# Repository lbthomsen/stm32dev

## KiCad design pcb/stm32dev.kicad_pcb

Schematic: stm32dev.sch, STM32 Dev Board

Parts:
C1, C3: 10uF; C_0805_2012Metric; LCSC C15850
C2, C5, C6, C7, C8, C14: 100nF; C_0402_1005Metric; LCSC C1525
C4: 1uF; C_0402_1005Metric; LCSC C52923
C9: 10nF; C_0402_1005Metric; LCSC C15195
C10, C11: 20pF; C_0402_1005Metric; LCSC C1554
C12, C13: 2.2uF; C_0603_1608Metric; LCSC C23630
D1, D5, D6, D7: WS2812C; LED_WS2812C-2020; LCSC C965556
D2: D_SOD-123; LCSC C8598
D3: GR; LED_0603_1608Metric; LCSC C72043
D4: BLUE; LED_0603_1608Metric; LCSC C72041
H1, H2, H3, H4: MountingHole_2.2mm_M2
J1: USB_C_Receptacle_HRO_TYPE-C-31-M-12; LCSC C165948
J2: PinHeader_2x03_P2.54mm_Horizontal
J3: Micro_SD_Card_Det; microSD_HC_Hirose_DM3D-SF
J4, J5: PinHeader_2x20_P2.54mm_Vertical
R1, R5: 10k; R_0402_1005Metric; LCSC C25744
R2, R3: 22R; R_0402_1005Metric; LCSC C25092
R6, R9: 220; R_0402_1005Metric; LCSC C25091
R7, R8: 5.1k; R_0402_1005Metric; LCSC C25905
SW1, SW2: TS-1088R-02526; LCSC C455281
U1: XC6206P332MR; SOT-23; LCSC C5446
U2: STM32F405RGTx; LQFP-64_10x10mm_P0.5mm; LCSC C15742
U3: W25Q128JVS; SOIC-8_5.23x5.23mm_P1.27mm
Y1: 16 MHz; Crystal_SMD_3225-4Pin_3.2x2.5mm; LCSC C13738

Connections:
+5V: C1.1, D2.1 (K), J5.37, J5.38, U1.3
BO0: R5.1, SW2.1, U2.60 (BOOT0)
GND: C1.2, C2.2, C3.2, C4.2, C5.2, C6.2, C7.2, C8.2, C9.2, C10.2, C11.2, C12.2, C13.2, C14.2, D1.2, D5.2, D6.2, D7.2, J1.A1, J1.A12, J1.B1, J1.B12, J1.S1, J2.5, J3.6 (VSS), J3.9 (DET_B), J3.11 (SHIELD), J4.1, J4.2, J4.39, J4.40, J5.39, J5.40, R5.2, R6.2, SW1.1, U1.1, U2.12 (VSSA), U2.18 (VSS), U2.63 (VSS), U3.4, Y1.2, Y1.4
NRST: C2.1, J2.1, R1.2, SW1.2, U2.7 (NRST)
unnamed: C10.1, U2.5 (PH0), Y1.1
unnamed: C11.1, U2.6 (PH1), Y1.3
unnamed: C12.1, U2.31 (VCAP_1)
unnamed: C13.1, U2.47 (VCAP_2)
unnamed: D1.1, D5.3
unnamed: D3.1, R6.1
unnamed: D4.1, R9.1
unnamed: D5.1, D6.3
unnamed: D6.1, D7.3
unnamed: J1.A5, R7.1
unnamed: J1.A6, J1.B6, R3.1
unnamed: J1.A7, J1.B7, R2.1
unnamed: J1.B5, R8.1
PA0: J4.11, J4.12, U2.14 (PA0)
PA1: J4.13, J4.14, U2.15 (PA1)
PA2: J4.15, J4.16, U2.16 (PA2)
PA3: J4.17, J4.18, U2.17 (PA3)
PA4: J4.19, J4.20, U2.20 (PA4)
PA5: J4.21, J4.22, U2.21 (PA5)
PA6: J4.23, J4.24, U2.22 (PA6)
PA7: J4.25, J4.26, U2.23 (PA7)
PA8: J5.23, J5.24, U2.41 (PA8)
PA9: J5.21, J5.22, U2.42 (PA9)
PA10: J5.19, J5.20, U2.43 (PA10)
PA11: J5.17, J5.18, R2.2, U2.44 (PA11)
PA12: J5.15, J5.16, R3.2, U2.45 (PA12)
PA15: J5.13, J5.14, U2.50 (PA15)
PB0: J4.31, J4.32, U2.26 (PB0)
PB1: J4.33, J4.34, U2.27 (PB1)
PB2: J4.35, J4.36, U2.28 (PB2)
PB3: U3.6
PB4: J5.11, J5.12, U2.56 (PB4), U3.2
PB5: J5.9, J5.10, U2.57 (PB5), U3.5
PB6: J5.7, J5.8, U2.58 (PB6), U3.1
PB7: J5.5, J5.6, U2.59 (PB7)
PB8: J5.3, J5.4, U2.61 (PB8)
PB9: J5.1, J5.2, U2.62 (PB9)
PB10: J5.35, J5.36, U2.29 (PB10)
PB11: J5.33, J5.34, U2.30 (PB11)
PB12: J5.31, J5.32, U2.33 (PB12)
PB13: J5.29, J5.30, U2.34 (PB13)
PB14: J5.27, J5.28, U2.35 (PB14)
PB15: J5.25, J5.26, U2.36 (PB15)
PC0: J4.3, J4.4, U2.8 (PC0)
PC1: J4.5, J4.6, U2.9 (PC1)
PC2: J4.7, J4.8, U2.10 (PC2)
PC3: J4.9, J4.10, U2.11 (PC3)
PC4: J4.27, J4.28, U2.24 (PC4)
PC5: J4.29, J4.30, U2.25 (PC5)
PC6: D1.3, U2.37 (PC6)
PC13: R9.2, U2.2 (PC13)
SD_CLK: J3.5 (CLK), U2.53 (PC12)
SD_CMD: J3.3 (CMD), U2.54 (PD2)
SD_D0: J3.7 (DAT0), U2.39 (PC8)
SD_D1: J3.8 (DAT1), U2.40 (PC9)
SD_D2: J3.1 (DAT2), U2.51 (PC10)
SD_D3: J3.2 (DAT3/CD), U2.52 (PC11)
SD_DET: J3.10 (DET_A), U2.38 (PC7)
SWCLK: J2.3, U2.49 (PA14)
SWDIO: J2.4, U2.46 (PA13)
SWO: J2.6, U2.55 (PB3)
UCC: R7.2, R8.2, U2.3 (PC14)
VBUS: D2.2 (A), J1.A4, J1.A9, J1.B4, J1.B9

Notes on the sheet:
USB C Connection

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
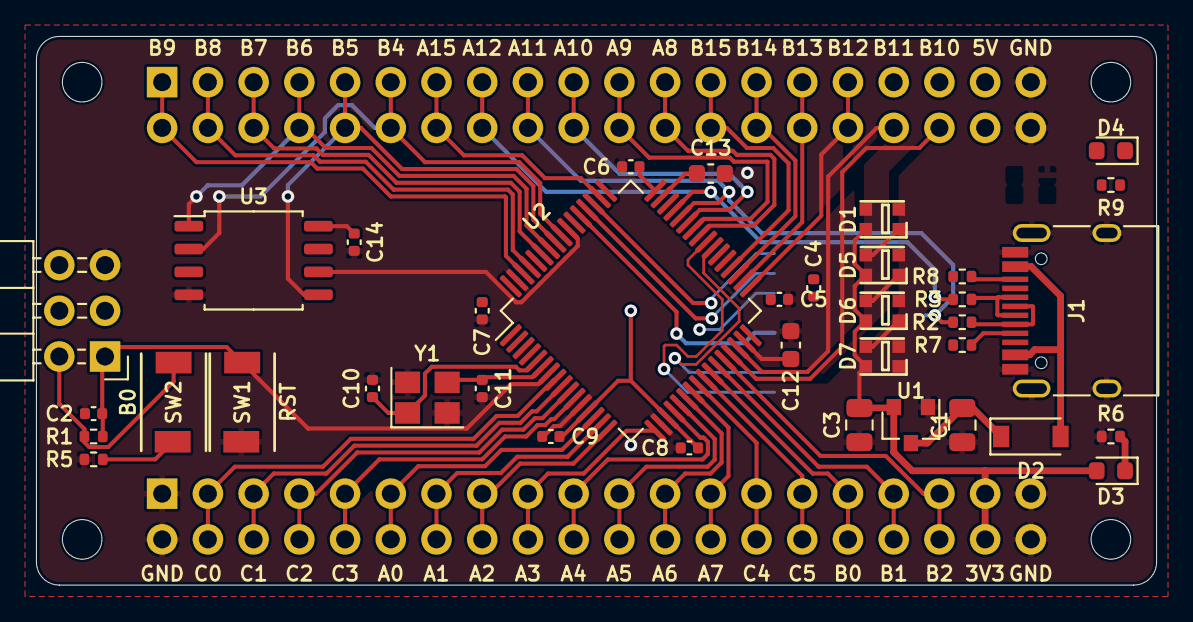
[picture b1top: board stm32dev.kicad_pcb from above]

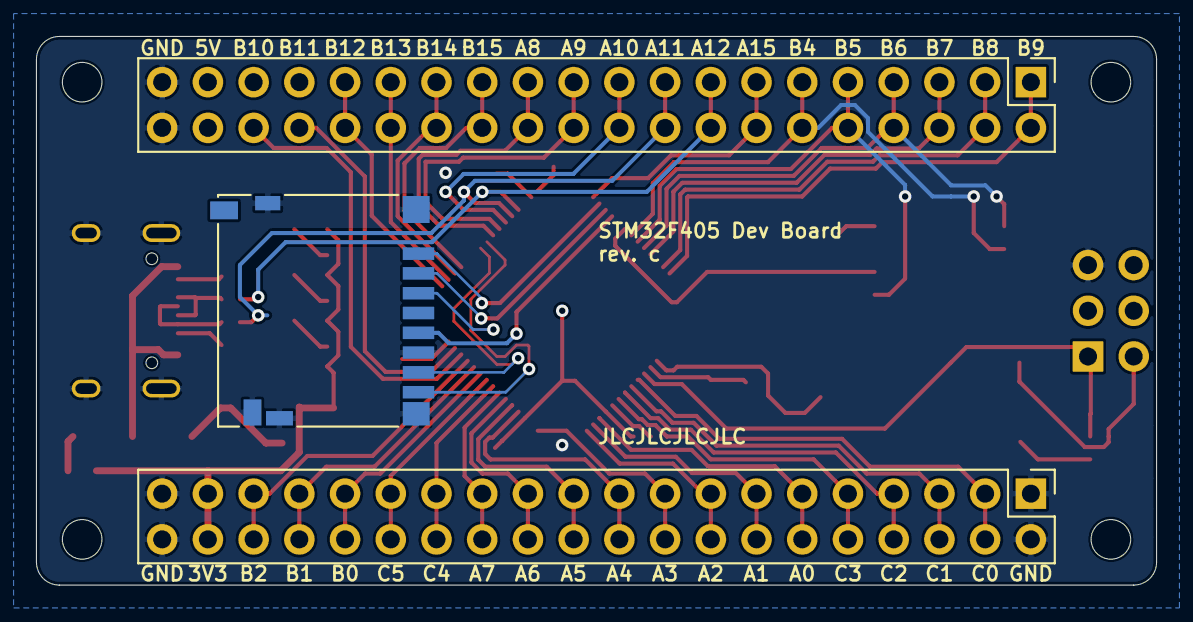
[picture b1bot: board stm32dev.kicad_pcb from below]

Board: 2 copper layers, 62.2 x 30.5 mm, 44 parts (3 on the bottom side), 67 nets.

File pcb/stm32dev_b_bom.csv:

Comment,Designator,Footprint,LCSC
"10uF","C1,C3","Capacitor_SMD:C_0805_2012Metric","C15850"
"20pF","C10,C11","Capacitor_SMD:C_0402_1005Metric","C1554"
"2.2uF","C13,C12","Capacitor_SMD:C_0402_1005Metric","C12530"
"1uF","C4","Capacitor_SMD:C_0402_1005Metric","C52923"
"100nF","C5,C6,C7,C8,C2","Capacitor_SMD:C_0402_1005Metric","C1525"
"10nF","C9","Capacitor_SMD:C_0402_1005Metric","C15195"
"WS2812B","D1","LED_SMD:LED_WS2812B_PLCC4_5.0x5.0mm_P3.2mm","C114586"
"~","D2","Diode_SMD:D_SOD-123","C8598"
"YEL","D3","LED_SMD:LED_0603_1608Metric","C72038"
"BLUE","D4","LED_SMD:LED_0603_1608Metric","C72041"
"USB_C_Receptacle_USB2.0","J1","Connector_USB:USB_C_Receptacle_HRO_TYPE-C-31-M-12","C167321"
"~","J2","Connector_PinHeader_2.54mm:PinHeader_2x03_P2.54mm_Horizontal"
"Micro_SD_Card_Det","J3","Connector_Card:microSD_HC_Hirose_DM3D-SF"
"~","J4,J5","Connector_PinHeader_2.54mm:PinHeader_2x20_P2.54mm_Vertical"
"NM","R1,R5","Resistor_SMD:R_0402_1005Metric"
"22R","R2,R3","Resistor_SMD:R_0402_1005Metric","C25092"
"1.5k","R4","Resistor_SMD:R_0402_1005Metric","C25867"
"5.1k","R7,R8","Resistor_SMD:R_0402_1005Metric","C25905"
"1k","R9,R6","Resistor_SMD:R_0402_1005Metric","C25905"
"~","SW1,SW2","Button_Switch_SMD:SW_SPST_TL3342","C318887"
"XC6206P332MR","U1","Package_TO_SOT_SMD:SOT-23","C5446"
"STM32F405RGTx","U2","Package_QFP:LQFP-64_10x10mm_P0.5mm","C15742"
"8 MHz","Y1","Crystal:Crystal_SMD_Abracon_ABM3-2Pin_5.0x3.2mm","C115962"

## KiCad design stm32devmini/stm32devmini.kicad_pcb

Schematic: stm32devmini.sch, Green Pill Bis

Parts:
C1, C2: 10uF; C_0805_2012Metric; LCSC C15850
C3, C6, C8, C9, C10: 100nF; C_0402_1005Metric; LCSC C1525
C5, C7, C11, C12: 20pF; C_0402_1005Metric; LCSC C1554
D1: D_SOD-123; LCSC C8598
D2: YEL; LED_0603_1608Metric; LCSC C72038
D3: BLUE; LED_0603_1608Metric; LCSC C72041
J1: USB_C_Receptacle_USB2.0; USB_C_Receptacle_HRO_TYPE-C-31-M-12; LCSC C167321
J2, J3: PinHeader_1x20_P2.54mm_Vertical
J4: PinHeader_1x04_P2.54mm_Horizontal
R1, R2: 22R; R_0402_1005Metric; LCSC C25092
R3: 1.5k; R_0402_1005Metric; LCSC C25867
R4, R5: 5.1k; R_0402_1005Metric; LCSC C25905
R6, R9: NM; R_0402_1005Metric
R7, R8: 1k; R_0402_1005Metric; LCSC C25905
SW1, SW2: SW_SPST_TL3342; LCSC C318887
U1: XC6206P332MR; SOT-23; LCSC C5446
U2: STM32F103C8T6; LQFP-48_7x7mm_P0.5mm; LCSC C8734
Y1: 8M; Crystal_SMD_Abracon_ABM3-2Pin_5.0x3.2mm; LCSC C115962
Y2: 32.768k; Crystal_SMD_EuroQuartz_EQ161-2Pin_3.2x1.5mm; LCSC C32346

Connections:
+3V3: C2.1, C6.1, C8.1, C9.1, C10.1, D2.2 (A), D3.2 (A), J2.18, J4.1, R3.2, R6.1, SW2.2, U1.2, U2.1 (VBAT), U2.9 (VDDA), U2.24 (VDD), U2.36 (VDD), U2.48 (VDD)
+5V: C1.1, D1.1 (K), J2.19, U1.3
A0: J2.5, U2.10 (PA0)
A1: J2.6, U2.11 (PA1)
A2: J2.7, U2.12 (PA2)
A3: J2.8, U2.13 (PA3)
A4: J2.9, U2.14 (PA4)
A5: J2.10, U2.15 (PA5)
A6: J2.11, U2.16 (PA6)
A7: J2.12, U2.17 (PA7)
A8: J3.16, U2.29 (PA8)
A9: J3.15, U2.30 (PA9)
A10: J3.14, U2.31 (PA10)
A11: J3.13, R1.2, U2.32 (PA11)
A12: J3.12, R2.2, U2.33 (PA12)
A15: J3.11, U2.38 (PA15)
B0: J2.13, U2.18 (PB0)
B1: J2.14, U2.19 (PB1)
B2: J2.15, U2.20 (PB2)
B3: J3.10, U2.39 (PB3)
B4: J3.9, U2.40 (PB4)
B5: J3.8, U2.41 (PB5)
B6: J3.7, U2.42 (PB6)
B7: J3.6, U2.43 (PB7)
B8: J3.5, U2.45 (PB8)
B9: J3.4, U2.46 (PB9)
B10: J2.16, U2.21 (PB10)
B11: J2.17, U2.22 (PB11)
B12: J3.20, U2.25 (PB12)
B13: J3.19, U2.26 (PB13)
B14: J3.18, U2.27 (PB14)
B15: J3.17, U2.28 (PB15)
BO0: J3.3, R9.1, SW2.1, U2.44 (BOOT0)
C13: J2.2, R7.2, U2.2 (PC13)
C14: C11.1, J2.3, U2.3 (PC14), Y2.1
C15: C12.1, J2.4, U2.4 (PC15), Y2.2
GND: C1.2, C2.2, C3.2, C5.2, C6.2, C7.2, C8.2, C9.2, C10.2, C11.2, C12.2, J1.A1, J1.A12, J1.B1, J1.B12, J1.S1, J2.1, J2.20, J3.1, J4.4, R4.2, R5.2, R8.2, R9.2, SW1.1, U1.1, U2.8 (VSSA), U2.23 (VSS), U2.35 (VSS), U2.47 (VSS)
unnamed: C5.1, U2.5 (PD0), Y1.1
unnamed: C7.1, U2.6 (PD1), Y1.2
unnamed: D2.1 (K), R8.1
unnamed: D3.1 (K), R7.1
unnamed: J1.A5, R5.1
unnamed: J1.A6, J1.B6, R2.1, R3.1
unnamed: J1.A7, J1.B7, R1.1
unnamed: J1.B5, R4.1
RST: C3.1, J3.2, R6.2, SW1.2, U2.7 (NRST)
SWCLK: J4.3, U2.37 (PA14)
SWDIO: J4.2, U2.34 (PA13)
VBUS: D1.2 (A), J1.A4, J1.A9, J1.B4, J1.B9

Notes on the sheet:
Internal pull-up
Power Regulation
Decoupling
USB C Connection
NOTICE! Headers are mostly but NOT 100 % compatible with the blue/black pill.

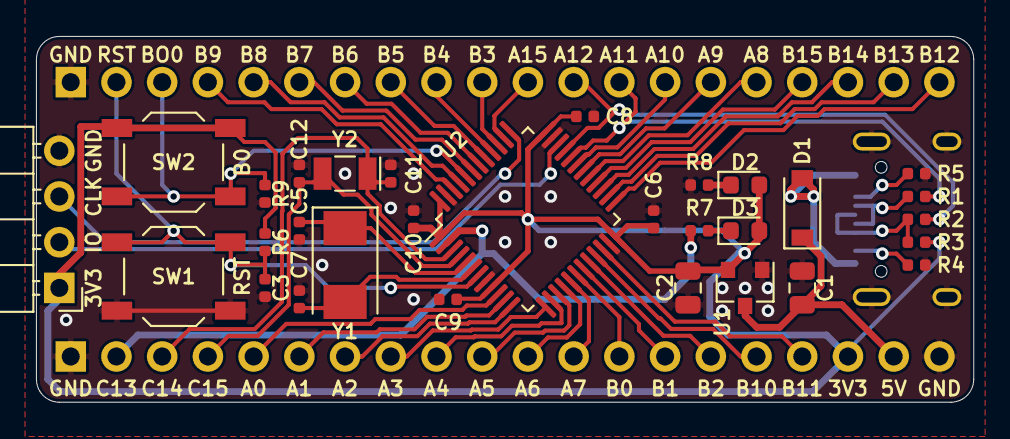
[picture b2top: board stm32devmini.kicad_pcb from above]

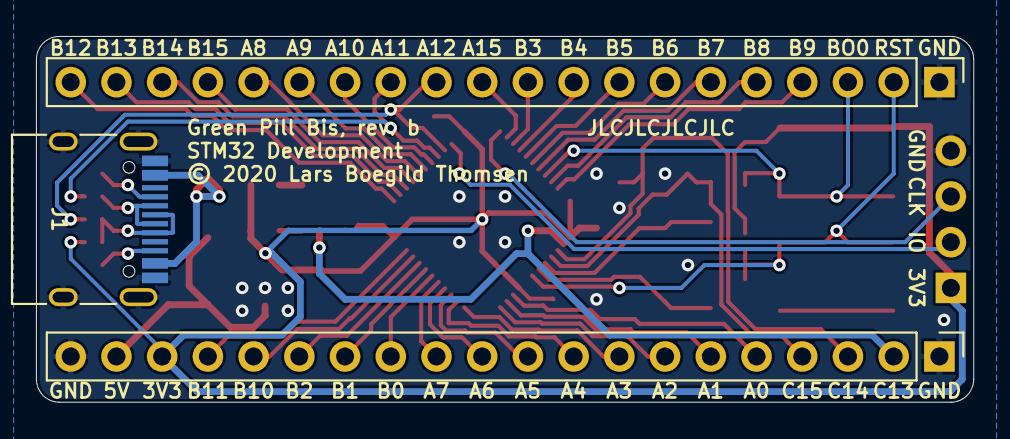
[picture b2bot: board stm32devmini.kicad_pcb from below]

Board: 2 copper layers, 52.1 x 20.3 mm, 33 parts (3 on the bottom side), 49 nets.

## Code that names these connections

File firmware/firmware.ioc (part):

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PC3.Mode=Full_Duplex_Master
PH0-OSC_IN.Signal=RCC_OSC_IN
Mcu.UserName=STM32F405RGTx
PB10.Mode=Full_Duplex_Master
PC12.Signal=SDIO_CK
PC10.Signal=SDIO_D2
PA12.GPIOParameters=GPIO_Speed
PB15.Signal=USB_OTG_HS_DP
PB13.Signal=CAN2_TX
RCC.SYSCLKSource=RCC_SYSCLKSOURCE_PLLCLK
PB5.GPIOParameters=GPIO_PuPd
PA12.Signal=GPIO_Output
PB6.Signal=I2C1_SCL
PC7.Signal=GPIO_Input
PB6.Mode=I2C
PC3.Signal=SPI2_MOSI
PH0-OSC_IN.Mode=HSE-External-Oscillator
RCC.HSE_VALUE=16000000
PB3.Mode=JTAG_5_pins
PA15.Mode=JTAG_5_pins
PB4.Mode=JTAG_5_pins
PA14.Mode=JTAG_5_pins
PB14.Mode=Device_Only_FS
PC9.Mode=SD_4_bits_Wide_bus
PB7.Signal=I2C1_SDA
PH1-OSC_OUT.Mode=HSE-External-Oscillator
Mcu.Package=LQFP64
PB9.Signal=CAN1_TX
PA6.Signal=ADCx_IN6
PB12.Mode=Slave
PA10.Signal=USART1_RX
PA15.Signal=SYS_JTDI
PC11.Mode=SD_4_bits_Wide_bus
PB13.Mode=Slave
PA12.GPIO_Speed=GPIO_SPEED_FREQ_LOW
PB4.Signal=SYS_JTRST
PA3.Signal=USART2_RX
PA10.Mode=Asynchronous
PC11.Signal=SDIO_D3
PC8.Signal=SDIO_D0
PC2.Signal=SPI2_MISO
PC6.Signal=GPIO_Input
PC10.Mode=SD_4_bits_Wide_bus
PC2.Mode=Full_Duplex_Master
PA13.Signal=SYS_JTMS-SWDIO
PA3.Mode=Asynchronous
PA9.Mode=Asynchronous
PB9.Mode=Master
PA9.Signal=USART1_TX
PB10.Signal=SPI2_SCK
PB14.Signal=USB_OTG_HS_DM
PD2.Mode=SD_4_bits_Wide_bus
PA5.Signal=COMP_DAC2_group
PC12.Mode=SD_4_bits_Wide_bus
board=custom
PB15.Mode=Device_Only_FS
PH1-OSC_OUT.Signal=RCC_OSC_OUT
PA13.Mode=JTAG_5_pins
Mcu.Name=STM32F405RGTx
PA2.Signal=USART2_TX
PC8.Mode=SD_4_bits_Wide_bus
PB3.Signal=SYS_JTDO-SWO
PA4.Signal=COMP_DAC1_group
RCC.SYSCLKFreq_VALUE=72000000
PB5.Signal=GPIO_Input
PB5.GPIO_PuPd=GPIO_PULLUP
PB7.Mode=I2C
PA14.Signal=SYS_JTCK-SWCLK
PB8.Mode=Master
PA2.Mode=Asynchronous
PB8.Signal=CAN1_RX
PC9.Signal=SDIO_D1
PD2.Signal=SDIO_CMD
PB12.Signal=CAN2_RX
PA7.Signal=ADCx_IN7

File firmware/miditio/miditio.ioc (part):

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Mcu.Name=STM32F405RGTx
Mcu.Package=LQFP64
Mcu.UserName=STM32F405RGTx
PA0-WKUP.Signal=ADCx_IN0
PA1.Signal=ADCx_IN1
PA10.Mode=Asynchronous
PA10.Signal=USART1_RX
PA11.Mode=Device_Only
PA11.Signal=USB_OTG_FS_DM
PA12.Mode=Device_Only
PA12.Signal=USB_OTG_FS_DP
PA13.Mode=Serial_Wire
PA13.Signal=SYS_JTMS-SWDIO
PA14.Mode=Serial_Wire
PA14.Signal=SYS_JTCK-SWCLK
PA4.Signal=COMP_DAC1_group
PA5.Signal=COMP_DAC2_group
PA9.Mode=Asynchronous
PA9.Signal=USART1_TX
PC13-ANTI_TAMP.GPIOParameters=PinState,GPIO_Label
PC13-ANTI_TAMP.GPIO_Label=LED
PC13-ANTI_TAMP.PinState=GPIO_PIN_SET
PC13-ANTI_TAMP.Signal=GPIO_Output
PH0-OSC_IN.Mode=HSE-External-Oscillator
PH0-OSC_IN.Signal=RCC_OSC_IN
PH1-OSC_OUT.Mode=HSE-External-Oscillator
PH1-OSC_OUT.Signal=RCC_OSC_OUT
RCC.HSE_VALUE=8000000
RCC.SYSCLKFreq_VALUE=168000000
RCC.SYSCLKSource=RCC_SYSCLKSOURCE_PLLCLK
board=custom

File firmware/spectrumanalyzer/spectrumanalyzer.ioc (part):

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Mcu.Name=STM32F405RGTx
Mcu.Package=LQFP64
Mcu.UserName=STM32F405RGTx
PA0-WKUP.Signal=ADCx_IN0
PA13.Mode=Serial_Wire
PA13.Signal=SYS_JTMS-SWDIO
PA14.Mode=Serial_Wire
PA14.Signal=SYS_JTCK-SWCLK
PA4.Signal=COMP_DAC1_group
PA5.Signal=COMP_DAC2_group
PA6.GPIOParameters=GPIO_Label
PA6.GPIO_Label=P0
PA6.Signal=ADCx_IN6
PA7.GPIOParameters=GPIO_Label
PA7.GPIO_Label=P1
PA7.Signal=ADCx_IN7
PC0.GPIOParameters=GPIO_Label
PC0.GPIO_Label=DBG0
PC0.Signal=GPIO_Output
PC1.GPIOParameters=GPIO_Label
PC1.GPIO_Label=DBG1
PC1.Signal=GPIO_Output
PC13-ANTI_TAMP.GPIOParameters=PinState,GPIO_Label
PC13-ANTI_TAMP.GPIO_Label=BUILTIN_LED
PC13-ANTI_TAMP.PinState=GPIO_PIN_SET
PC13-ANTI_TAMP.Signal=GPIO_Output
PH0-OSC_IN.Mode=HSE-External-Oscillator
PH0-OSC_IN.Signal=RCC_OSC_IN
PH1-OSC_OUT.Mode=HSE-External-Oscillator
PH1-OSC_OUT.Signal=RCC_OSC_OUT
RCC.HSE_VALUE=8000000
RCC.SYSCLKFreq_VALUE=168000000
RCC.SYSCLKSource=RCC_SYSCLKSOURCE_PLLCLK
board=custom

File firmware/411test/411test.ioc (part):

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Mcu.Name=STM32F411C(C-E)Ux
Mcu.Package=UFQFPN48
Mcu.UserName=STM32F411CEUx
PA13.Mode=Trace_Asynchronous_SW
PA13.Signal=SYS_JTMS-SWDIO
PA14.Mode=Trace_Asynchronous_SW
PA14.Signal=SYS_JTCK-SWCLK
PA6.Signal=S_TIM3_CH1
PB3.Mode=Trace_Asynchronous_SW
PB3.Signal=SYS_JTDO-SWO
PC13-ANTI_TAMP.Signal=GPIO_Output
PC14-OSC32_IN.Signal=GPIO_Output
PC15-OSC32_OUT.Signal=GPIO_Output
PH0\ -\ OSC_IN.Mode=HSE-External-Oscillator
PH0\ -\ OSC_IN.Signal=RCC_OSC_IN
PH1\ -\ OSC_OUT.Mode=HSE-External-Oscillator
PH1\ -\ OSC_OUT.Signal=RCC_OSC_OUT
RCC.HSE_VALUE=25000000
RCC.SYSCLKFreq_VALUE=100000000
RCC.SYSCLKSource=RCC_SYSCLKSOURCE_PLLCLK
board=custom

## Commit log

2020-06-20 Hmmm
2020-06-23 Added .gitignore
2020-06-25 Hmmmm
2020-07-01 Almost ready
2020-07-03 stdm rev a
2020-07-20 Hmmmmm
2020-08-04 Removed old stuff
2020-08-04 Flipped caps
2020-08-04 Added cap
2020-08-04 Changed 2.2uF caps to 0603
2020-08-04 Cosmetic
2020-08-05 Shifted cpu sideways
2020-08-06 Hmmmm - minor cosmetic changes
2020-08-12 Test
2020-08-12 Few tweaks towards rev c
2020-08-13 Few cosmetics
2020-08-13 A few more mostly cosmetic tweaks
2020-08-14 Added firmware
2020-08-15 More firmware
2020-08-15 Added a few thermal vias
2020-08-20 Messing with pwm/dma
2020-10-19 Refactored code for simpler timing setting.
2020-10-20 WORKING!
2020-10-25 Optimized version working
2020-10-25 Using zeros buffer memcpy
2020-10-25 Forgot to save
2020-10-27 Fixed bug
2020-11-10 Added st7789
2020-11-10 Added stm32-st7789 sub module
2020-11-11 Moved branch to master
2020-11-11 Updated submodule
2020-11-14 Working
2020-11-16 Requesting 500 mA from USB
2020-12-11 Added sd example
2020-12-22 Cleaned up old code
2021-01-23 Also working
2021-02-16 Still not quite there but almost
2021-03-14 Removed all the wireless stuff - back to rev b
2021-05-11 Foobar
2022-08-20 Playing with adc dac
2022-08-31 Playing with automatic ADC/DAC calibration
2022-09-01 USB MIDI Example working

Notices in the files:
stm32devmini/stm32devmini.kicad_pcb:
© 2020 Lars Boegild Thomsen
